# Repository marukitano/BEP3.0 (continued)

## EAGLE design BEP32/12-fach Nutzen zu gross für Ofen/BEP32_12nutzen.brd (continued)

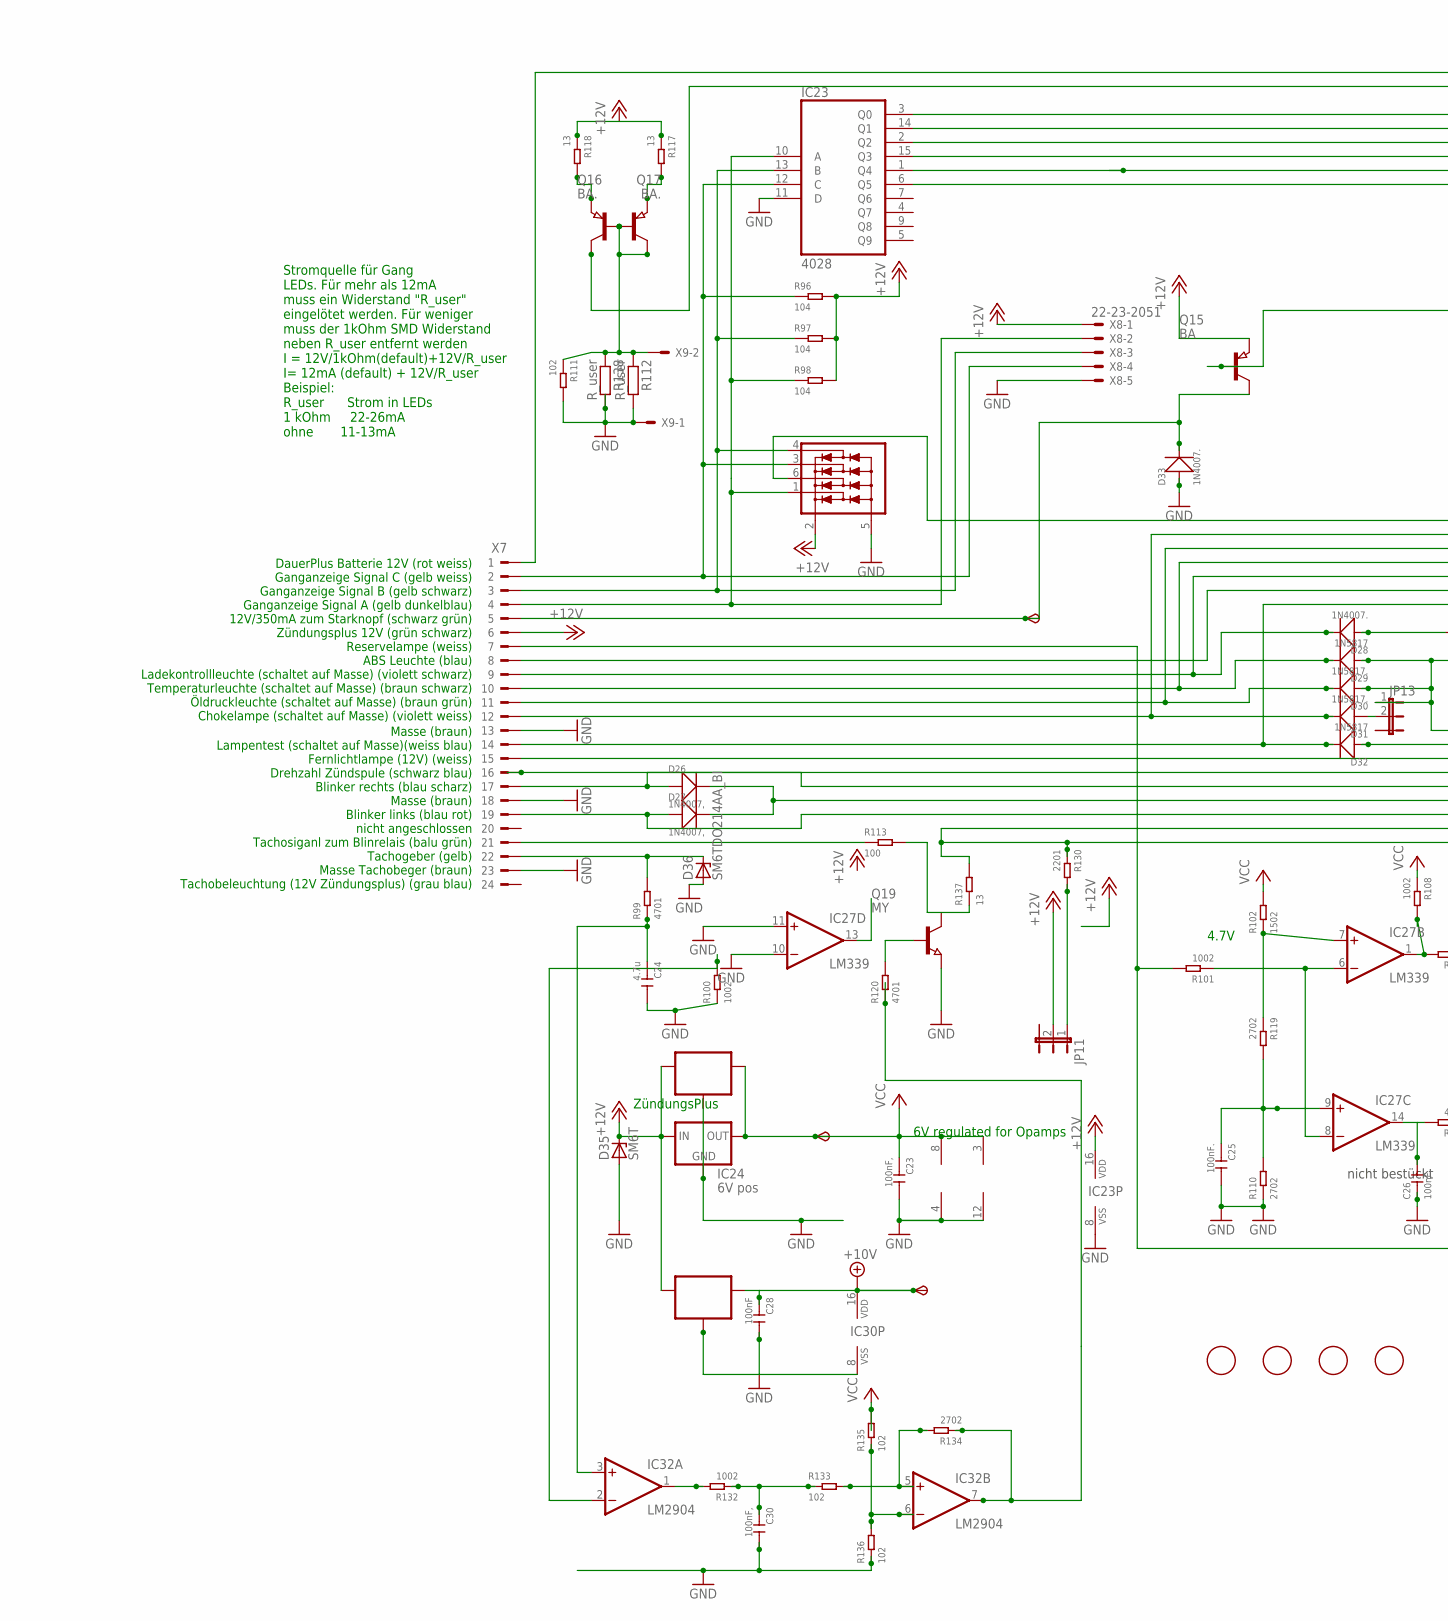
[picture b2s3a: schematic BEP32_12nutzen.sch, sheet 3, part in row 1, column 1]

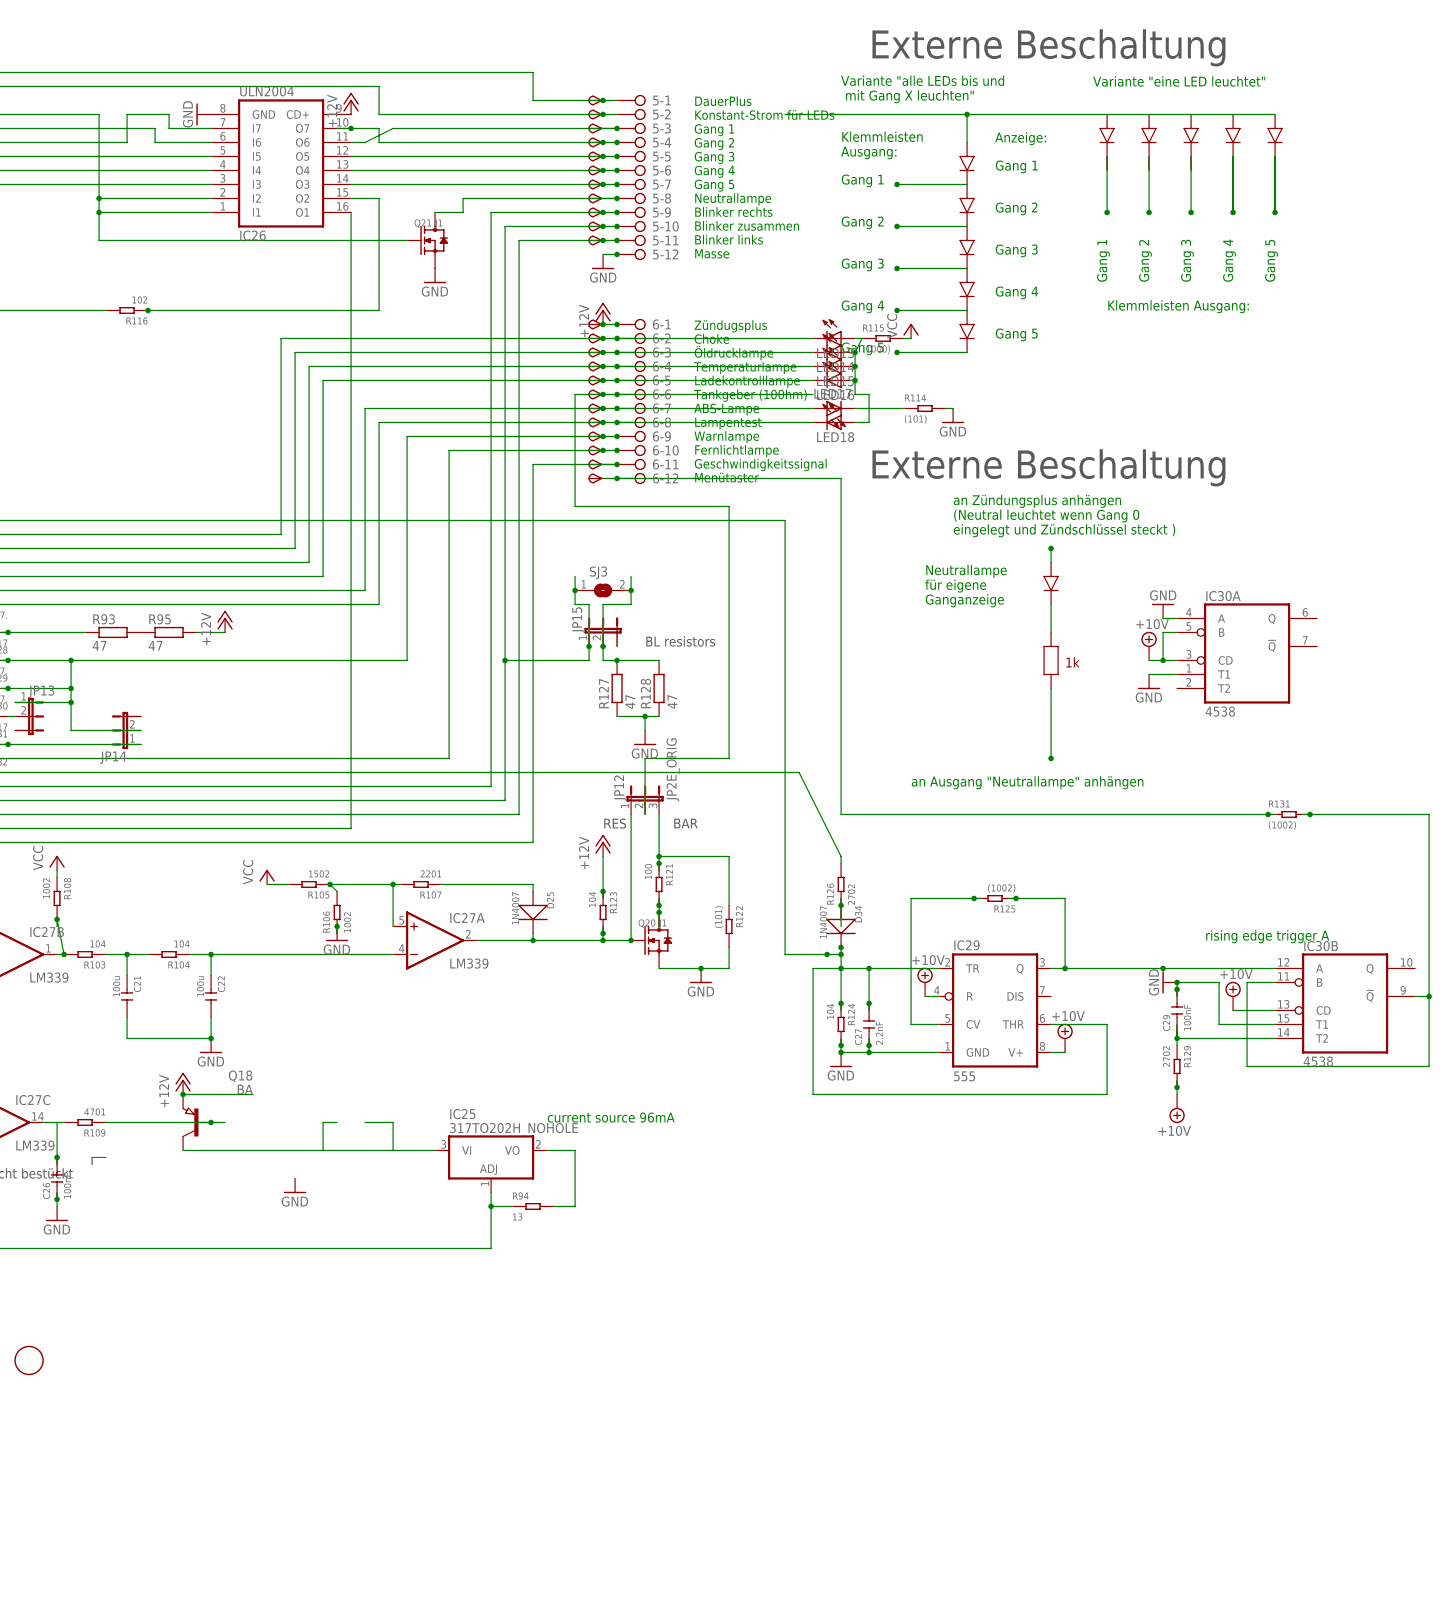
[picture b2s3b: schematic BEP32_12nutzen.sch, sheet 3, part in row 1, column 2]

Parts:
5, 6: 2081-1132; 12-PIN
6V2, 10V2: TPSB2.0; B2.0
C21, C22: 100u; C1206
C23, C30: 100nF,; C0805
C24: 4.7u; C0805
C25, C26: 100nF.; C0805
C27: 2.2nF; C0805
C28, C29: 100nF; C0805
D25, D34: 1N4007; DO-214AC
D26, D27: 1N4007,; DO-214AC
D28, D33: 1N4007.; DO-214AC
D29, D32: 1N5817; DO-214AC_SLIM
D30, D31: 1N5817.; DO-214AC_SLIM
D35: SM6T; DO214AA
D36: SM6TDO214AA_BI; DO214AA_BI
FID9, FID10, FID11, FID12: FIDUCIAL; FIDUCIAL_1MM
IC23: 4028; SO16
IC24: 6V pos; 78LXX
IC25: 317TO202H_NOHOLE; TO220H_NOHOLE
IC26: ULN2004; SO16
IC27: LM339; SO14
IC28: 78L06; SOT89_ROUND
IC29: 555; SO08
IC30: 4538; SO16
IC31: 78L10; SOT89_ROUND
IC32: LM2904; SO08
IC33: NUP4304SOT457_R; SOT457R_PHILIPS
JP11, JP13, JP14, JP15: JP2EJP2_SMALLPADS; JP2_SMALLPADS
JP12: JP2E_ORIG; JP2_ORIG_SMALLPADS
LED13, LED14, LED15, LED16, LED17, LED18: LEDLD260; LD260
Q15, Q18: BA; SOT89
Q16, Q17: BA.; SOT89
Q19: MY; SOT89
Q20, Q21: J1; SOT-23
R93, R95, R127, R128: 47; V235/17_1MM
R94, R117, R118, R137: 13; R1206
R96, R97, R98, R103, R104, R123, R124: 104; R0805
R99, R109, R120: 4701; R0805
R100, R101, R106, R108, R132: 1002; R0805
R102, R105: 1502; R0805
R107, R130: 2201; R0805
R110, R119, R126, R129, R134: 2702; R0805
R111, R116, R133, R135, R136: 102; R0805
R112, R138: R_user; R0805
R113, R121: 100; R0805
R114, R122: (101); R0805
R115: (1000); R0805
R125, R131: (1002); R0805
SJ3: SJ
START2: TPSB2.0; B2.0
TP47, TP48, TP49, TP50, TP51, TP52, TP53, TP54, TP55, TP56, TP57, TP58, TP59, TP60, TP61, TP62, TP63, TP64, TP66, TP67, TP68, TP69: TPSB2.0; B2.0
TP65: TPSB1,27; B1,27
X7: CON_BMWV2; 24-PIN_V2
X8: 22-23-2051
X9: 22-23-2021

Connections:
+10V: 10V2.TP, C28.1, IC29.4 (R), IC29.8 (V+), IC30.3 (CD), IC30.5 (B), IC30.13 (CD), IC30.16 (VDD), IC31.1 (OUT), R129.2; also elsewhere on the board
+12V: 6.1, D35.C, IC23.16 (VDD), IC24.IN, IC26.9 (CD+), IC28.3 (IN), IC31.3 (IN), IC33.2 (V+), JP11.2, Q15.3 (E), Q18.3 (E), R95.2, R96.2, R97.2, R98.2, R117.1, R118.1, R123.1, TP68.TP, X7.6, X8.1; also elsewhere on the board
+12V3: IC32.7 (OUT), R120.1, R134.1
GND: 5.12, C21.2, C22.2, C23.2, C24.2, C25.2, C26.1, C27.1, C28.2, C29.2, C30.2, D33.1 (+), D35.A, D36.A, IC23.8 (VSS), IC23.11 (D), IC24.GND, IC26.8 (GND), IC27.10 (-IN), IC27.11 (+IN), IC27.12 (GND), IC28.2 (GND), IC28.2@1 (GND), IC29.1 (GND), IC30.1 (T1), IC30.4 (A), IC30.8 (VSS), IC30.15 (T1), IC31.2 (GND), IC31.2@1 (GND), IC32.4 (V-), IC33.5 (V-), Q19.3 (E), Q20.2 (S), Q21.2 (S), R100.1, R106.1, R110.1, R111.2, R112.2, R114.2, R122.2, R124.2, R127.1, R128.1, R136.1, R138.2, X7.13, X7.18, X7.23, X8.5, X9.1; also elsewhere on the board
unnamed: R93.2, R95.1
unnamed: 6.9, D29.1 (+), D30.1 (+), JP13.1, JP14.2, TP65.TP
unnamed: IC23.10 (A), IC33.1 (D1), R98.1, X7.4, X8.2
unnamed: IC23.13 (B), IC33.4 (D4), R97.1, X7.3, X8.3
unnamed: D33.2 (-), Q15.2 (C), START2.TP, X7.5
unnamed: IC23.12 (C), IC33.3 (D3), R96.1, X7.2, X8.4
unnamed: 6.7, LED17.A, TP63.TP, X7.8
unnamed: 6.2, D31.2 (-), LED13.K (C), TP58.TP, X7.12
unnamed: 6.3, D30.2 (-), LED14.K (C), TP59.TP, X7.11
unnamed: 6.4, D29.2 (-), LED15.K (C), TP60.TP, X7.10
unnamed: 6.8, D32.2 (-), LED18.K (C), TP64.TP, X7.14
unnamed: 5.9, D26.1 (+), TP55.TP, X7.17
unnamed: 5.11, D27.1 (+), TP57.TP, X7.19
unnamed: D36.C, R99.2, X7.22
unnamed: C24.1, IC32.3 (+IN), R99.1
unnamed: 6.11, IC26.16 (O1), R130.1, R137.2, TP67.TP
unnamed: IC27.1 (OUT), R103.2, R108.2
unnamed: C21.1, R103.1, R104.2
unnamed: C22.1, IC27.4 (-IN), R104.1
unnamed: IC27.5 (+IN), R105.1, R106.2, R107.2
unnamed: D25.1 (+), R107.1
unnamed: C25.1, IC27.9 (+IN), R110.2, R119.2
unnamed: C26.2, IC27.14 (OUT), R109.2
unnamed: Q18.1 (B), R109.1
unnamed: IC23.2 (Q2), IC26.7 (I7)
unnamed: 5.5, IC26.12 (O5), TP51.TP
unnamed: IC23.1 (Q4), IC26.4 (I4)
unnamed: 5.8, Q21.3 (D), TP54.TP
unnamed: 6.10, TP66.TP, X7.15
unnamed: 6.5, D28.2 (-), LED16.K (C), TP61.TP, X7.9
unnamed: D28.1 (+), R93.1
unnamed: IC23.6 (Q5), IC26.3 (I3)
unnamed: 5.4, IC26.10 (O7), TP50.TP
unnamed: IC25.1 (ADJ), R94.1, R101.2, X7.7
unnamed: IC27.6 (-IN), IC27.8 (-IN), R101.1
unnamed: 5.2, Q17.2 (C), TP48.TP
unnamed: 5.1, TP47.TP, X7.1
unnamed: R126.2, X7.16
unnamed: IC23.15 (Q3), IC26.5 (I5)
unnamed: 5.6, IC26.13 (O4), TP52.TP
unnamed: 5.7, IC26.14 (O3), TP53.TP
unnamed: 6.6, JP12.2, TP62.TP
unnamed: LED17.K (C), R114.1
unnamed: LED13.A, LED14.A, LED15.A, LED16.A, LED18.A, R115.1
unnamed: Q15.1 (B), R116.2
unnamed: IC23.3 (Q0), IC26.1 (I1), IC26.2 (I2), Q21.1 (G)
unnamed: IC23.14 (Q1), IC26.6 (I6)
unnamed: 5.3, IC26.11 (O6), TP49.TP
unnamed: Q16.1 (B), Q16.2 (C), Q17.1 (B), R111.1, R112.1, R138.1, X9.2
unnamed: Q17.3 (E), R118.2
unnamed: Q16.3 (E), R117.2
unnamed: IC27.7 (+IN), R102.1, R119.1
unnamed: IC32.2 (-IN), R100.2
unnamed: Q19.1 (B), R120.2
unnamed: Q20.3 (D), R121.2
unnamed: IC25.2 (VO), R94.2
unnamed: IC25.3 (VI), Q18.2 (C)
unnamed: C27.2, D34.2 (-), IC29.2 (TR), IC29.6 (THR), IC33.6 (D2), R124.1
unnamed: IC29.5 (CV), R125.2
unnamed: IC29.3 (Q), IC30.12 (A), R125.1
unnamed: D34.1 (+), R126.1
unnamed: 5.10, D26.2 (-), D27.2 (-), JP15.1, SJ3.1, TP56.TP
unnamed: JP15.2, R127.2, R128.2, SJ3.2
unnamed: IC30.9 (!Q), IC30.11 (B), R131.2
unnamed: C29.1, IC30.14 (T2), R129.1
unnamed: JP11.1, R130.2
unnamed: IC26.15 (O2), R116.1
unnamed: 6.12, R131.1, TP69.TP
unnamed: D31.1 (+), JP13.2
unnamed: D25.2 (-), IC27.2 (OUT), JP12.1, Q20.1 (G), R123.2
unnamed: IC32.1 (OUT), R132.2
unnamed: C30.1, R132.1, R133.1
unnamed: IC32.5 (+IN), R133.2, R134.2
unnamed: IC32.6 (-IN), R135.1, R136.2
unnamed: D32.1 (+), JP14.1
unnamed: JP12.3, R121.1, R122.1
unnamed: R113.1, X7.21
unnamed: Q19.2 (C), R113.2, R137.1
VCC: 6V2.TP, C23.1, IC24.OUT, IC27.3 (V+), IC28.1 (OUT), IC32.8 (V+), R102.2, R105.2, R108.1, R115.2, R135.2; also elsewhere on the board

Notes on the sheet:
6V regulated for Opamps
current source 96mA
ZündungsPlus
Zündugsplus Choke Öldrucklampe Temperaturlampe Ladekontrolllampe Tankgeber (100hm) ABS-Lampe Lampentest Warnlampe Fernlichtlampe Geschwindigkeitssignal Menütaster
DauerPlus Konstant-Strom für LEDs Gang 1 Gang 2 Gang 3 Gang 4 Gang 5 Neutrallampe Blinker rechts Blinker zusammen Blinker links Masse
DauerPlus Batterie 12V (rot weiss) Ganganzeige Signal C (gelb weiss) Ganganzeige Signal B (gelb schwarz) Ganganzeige Signal A (gelb dunkelblau) 12V/350mA zum Starknopf (schwarz grün) Zündungsplus 12V (grün schwarz) Reservelampe (weiss) ABS Leuchte (blau) Ladekontrollleuchte (schaltet auf Masse) (vi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
Masse (braun) Lampentest (schaltet auf Masse)(weiss blau) Fernlichtlampe (12V) (weiss) Drehzahl Zündspule (schwarz blau) Blinker rechts (blau scharz) Masse (braun) Blinker links (blau rot) nicht angeschlossen Tachosiganl zum Blinrelais (balu grün) Tachogeber (gelb) Masse Tachobeger (braun) Tachobel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
4.7V
Stromquelle für Gang LEDs. Für mehr als 12mA muss ein Widerstand "R_user" eingelötet werden. Für weniger muss der 1kOhm SMD Widerstand neben R_user entfernt werden I = 12V/1kOhm(default)+12V/R_user I= 12mA (default) + 12V/R_user Beispiel: R_user Strom in LEDs 1 kOhm 22-26mA ohne 11-13mA
Gang 1
Gang 2
Gang 3
Gang 4
Gang 5
Variante "eine LED leuchtet"
Variante "alle LEDs bis und mit Gang X leuchten"
Klemmleisten Ausgang:
Klemmleisten Ausgang:
an Zündungsplus anhängen (Neutral leuchtet wenn Gang 0 eingelegt und Zündschlüssel steckt )
an Ausgang "Neutrallampe" anhängen
Neutrallampe für eigene Ganganzeige
Externe Beschaltung
Anzeige:
nicht bestückt
rising edge trigger A
BAR
RES
BL resistors

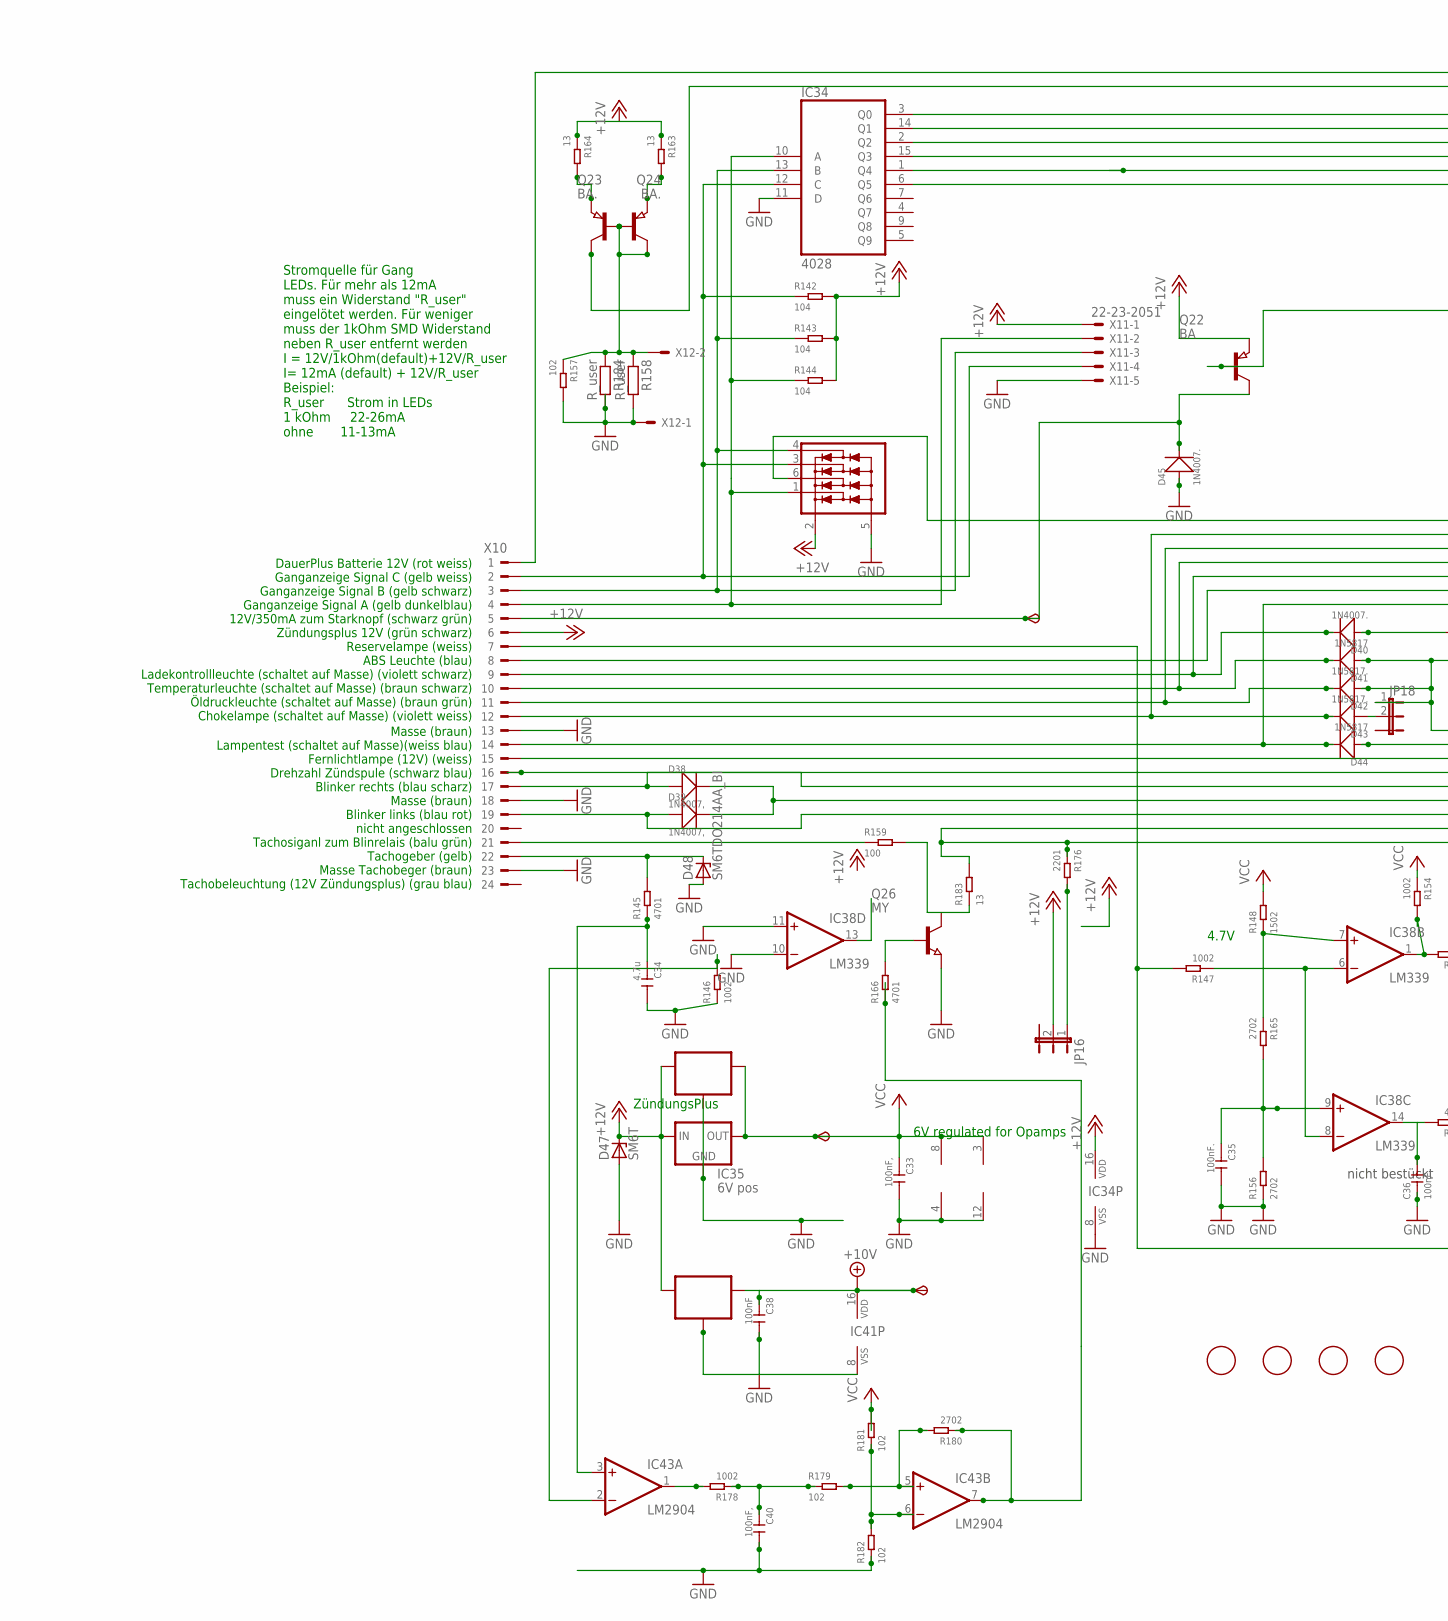
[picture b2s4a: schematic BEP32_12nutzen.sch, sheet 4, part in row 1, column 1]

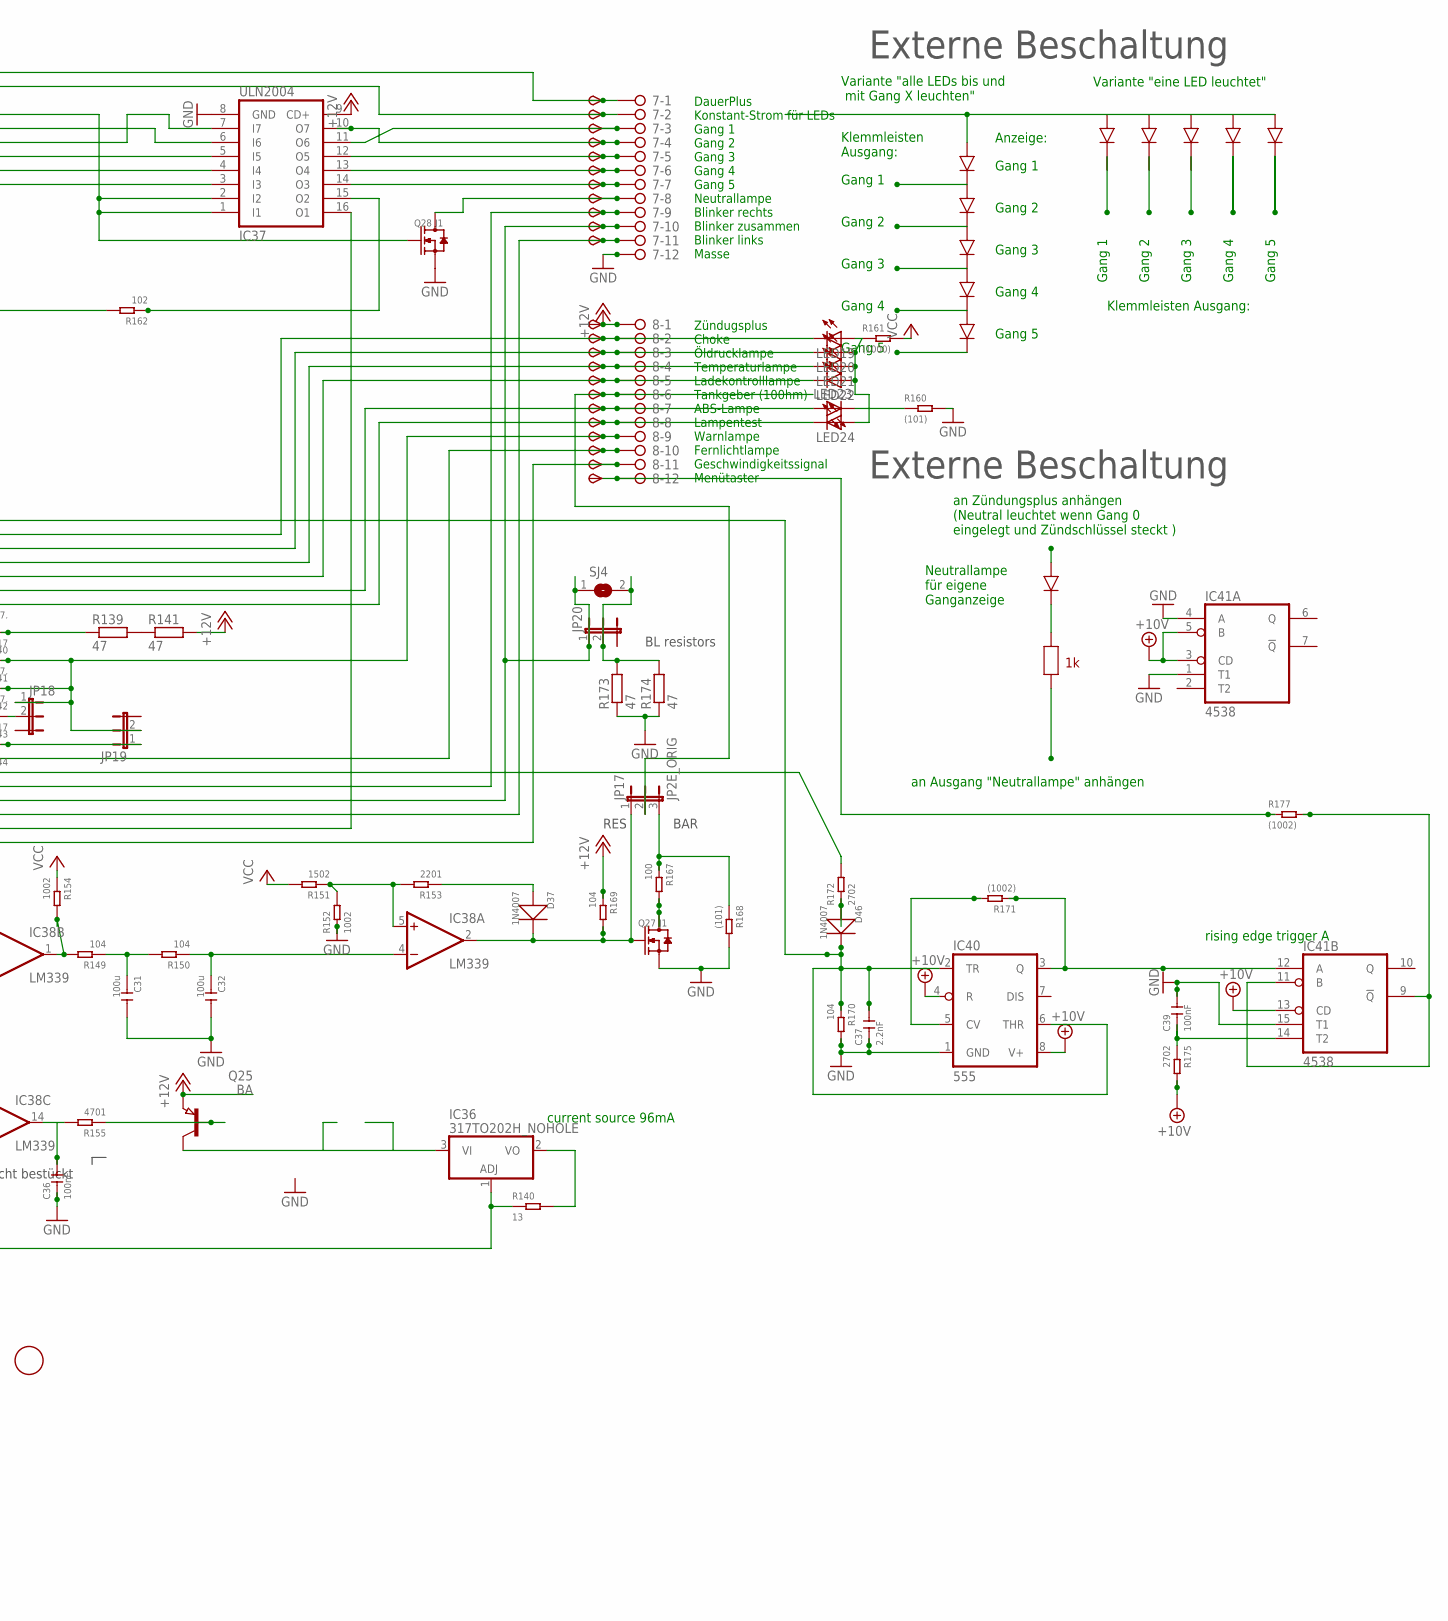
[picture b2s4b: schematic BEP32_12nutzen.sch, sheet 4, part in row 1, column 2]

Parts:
6V3, 10V3: TPSB2.0; B2.0
7, 8: 2081-1132; 12-PIN
C31, C32: 100u; C1206
C33, C40: 100nF,; C0805
C34: 4.7u; C0805
C35, C36: 100nF.; C0805
C37: 2.2nF; C0805
C38, C39: 100nF; C0805
D37, D46: 1N4007; DO-214AC
D38, D39: 1N4007,; DO-214AC
D40, D45: 1N4007.; DO-214AC
D41, D44: 1N5817; DO-214AC_SLIM
D42, D43: 1N5817.; DO-214AC_SLIM
D47: SM6T; DO214AA
D48: SM6TDO214AA_BI; DO214AA_BI
FID13, FID14, FID15, FID16: FIDUCIAL; FIDUCIAL_1MM
IC34: 4028; SO16
IC35: 6V pos; 78LXX
IC36: 317TO202H_NOHOLE; TO220H_NOHOLE
IC37: ULN2004; SO16
IC38: LM339; SO14
IC39: 78L06; SOT89_ROUND
IC40: 555; SO08
IC41: 4538; SO16
IC42: 78L10; SOT89_ROUND
IC43: LM2904; SO08
IC44: NUP4304SOT457_R; SOT457R_PHILIPS
JP16, JP18, JP19, JP20: JP2EJP2_SMALLPADS; JP2_SMALLPADS
JP17: JP2E_ORIG; JP2_ORIG_SMALLPADS
LED19, LED20, LED21, LED22, LED23, LED24: LEDLD260; LD260
Q22, Q25: BA; SOT89
Q23, Q24: BA.; SOT89
Q26: MY; SOT89
Q27, Q28: J1; SOT-23
R139, R141, R173, R174: 47; V235/17_1MM
R140, R163, R164, R183: 13; R1206
R142, R143, R144, R149, R150, R169, R170: 104; R0805
R145, R155, R166: 4701; R0805
R146, R147, R152, R154, R178: 1002; R0805
R148, R151: 1502; R0805
R153, R176: 2201; R0805
R156, R165, R172, R175, R180: 2702; R0805
R157, R162, R179, R181, R182: 102; R0805
R158, R184: R_user; R0805
R159, R167: 100; R0805
R160, R168: (101); R0805
R161: (1000); R0805
R171, R177: (1002); R0805
SJ4: SJ
START3: TPSB2.0; B2.0
TP70, TP71, TP72, TP73, TP74, TP75, TP76, TP77, TP78, TP79, TP80, TP81, TP82, TP83, TP84, TP85, TP86, TP87, TP89, TP90, TP91, TP92: TPSB2.0; B2.0
TP88: TPSB1,27; B1,27
X10: CON_BMWV2; 24-PIN_V2
X11: 22-23-2051
X12: 22-23-2021

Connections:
+10V: 10V3.TP, C38.1, IC40.4 (R), IC40.8 (V+), IC41.3 (CD), IC41.5 (B), IC41.13 (CD), IC41.16 (VDD), IC42.1 (OUT), R175.2; also elsewhere on the board
+12V: 8.1, D47.C, IC34.16 (VDD), IC35.IN, IC37.9 (CD+), IC39.3 (IN), IC42.3 (IN), IC44.2 (V+), JP16.2, Q22.3 (E), Q25.3 (E), R141.2, R142.2, R143.2, R144.2, R163.1, R164.1, R169.1, TP91.TP, X10.6, X11.1; also elsewhere on the board
+12V4: IC43.7 (OUT), R166.1, R180.1
GND: 7.12, C31.2, C32.2, C33.2, C34.2, C35.2, C36.1, C37.1, C38.2, C39.2, C40.2, D45.1 (+), D47.A, D48.A, IC34.8 (VSS), IC34.11 (D), IC35.GND, IC37.8 (GND), IC38.10 (-IN), IC38.11 (+IN), IC38.12 (GND), IC39.2 (GND), IC39.2@1 (GND), IC40.1 (GND), IC41.1 (T1), IC41.4 (A), IC41.8 (VSS), IC41.15 (T1), IC42.2 (GND), IC42.2@1 (GND), IC43.4 (V-), IC44.5 (V-), Q26.3 (E), Q27.2 (S), Q28.2 (S), R146.1, R152.1, R156.1, R157.2, R158.2, R160.2, R168.2, R170.2, R173.1, R174.1, R182.1, R184.2, X10.13, X10.18, X10.23, X11.5, X12.1; also elsewhere on the board
unnamed: R139.2, R141.1
unnamed: 8.9, D41.1 (+), D42.1 (+), JP18.1, JP19.2, TP88.TP
unnamed: IC34.10 (A), IC44.1 (D1), R144.1, X10.4, X11.2
unnamed: IC34.13 (B), IC44.4 (D4), R143.1, X10.3, X11.3
unnamed: D45.2 (-), Q22.2 (C), START3.TP, X10.5
unnamed: IC34.12 (C), IC44.3 (D3), R142.1, X10.2, X11.4
unnamed: 8.7, LED23.A, TP86.TP, X10.8
unnamed: 8.2, D43.2 (-), LED19.K (C), TP81.TP, X10.12
unnamed: 8.3, D42.2 (-), LED20.K (C), TP82.TP, X10.11
unnamed: 8.4, D41.2 (-), LED21.K (C), TP83.TP, X10.10
unnamed: 8.8, D44.2 (-), LED24.K (C), TP87.TP, X10.14
unnamed: 7.9, D38.1 (+), TP78.TP, X10.17
unnamed: 7.11, D39.1 (+), TP80.TP, X10.19
unnamed: D48.C, R145.2, X10.22
unnamed: C34.1, IC43.3 (+IN), R145.1
unnamed: 8.11, IC37.16 (O1), R176.1, R183.2, TP90.TP
unnamed: IC38.1 (OUT), R149.2, R154.2
unnamed: C31.1, R149.1, R150.2
unnamed: C32.1, IC38.4 (-IN), R150.1
unnamed: IC38.5 (+IN), R151.1, R152.2, R153.2
unnamed: D37.1 (+), R153.1
unnamed: C35.1, IC38.9 (+IN), R156.2, R165.2
unnamed: C36.2, IC38.14 (OUT), R155.2
unnamed: Q25.1 (B), R155.1
unnamed: IC34.2 (Q2), IC37.7 (I7)
unnamed: 7.5, IC37.12 (O5), TP74.TP
unnamed: IC34.1 (Q4), IC37.4 (I4)
unnamed: 7.8, Q28.3 (D), TP77.TP
unnamed: 8.10, TP89.TP, X10.15
unnamed: 8.5, D40.2 (-), LED22.K (C), TP84.TP, X10.9
unnamed: D40.1 (+), R139.1
unnamed: IC34.6 (Q5), IC37.3 (I3)
unnamed: 7.4, IC37.10 (O7), TP73.TP
unnamed: IC36.1 (ADJ), R140.1, R147.2, X10.7
unnamed: IC38.6 (-IN), IC38.8 (-IN), R147.1
unnamed: 7.2, Q24.2 (C), TP71.TP
unnamed: 7.1, TP70.TP, X10.1
unnamed: R172.2, X10.16
unnamed: IC34.15 (Q3), IC37.5 (I5)
unnamed: 7.6, IC37.13 (O4), TP75.TP
unnamed: 7.7, IC37.14 (O3), TP76.TP
unnamed: 8.6, JP17.2, TP85.TP
unnamed: LED23.K (C), R160.1
unnamed: LED19.A, LED20.A, LED21.A, LED22.A, LED24.A, R161.1
unnamed: Q22.1 (B), R162.2
unnamed: IC34.3 (Q0), IC37.1 (I1), IC37.2 (I2), Q28.1 (G)
unnamed: IC34.14 (Q1), IC37.6 (I6)
unnamed: 7.3, IC37.11 (O6), TP72.TP
unnamed: Q23.1 (B), Q23.2 (C), Q24.1 (B), R157.1, R158.1, R184.1, X12.2
unnamed: Q24.3 (E), R164.2
unnamed: Q23.3 (E), R163.2
unnamed: IC38.7 (+IN), R148.1, R165.1
unnamed: IC43.2 (-IN), R146.2
unnamed: Q26.1 (B), R166.2
unnamed: Q27.3 (D), R167.2
unnamed: IC36.2 (VO), R140.2
unnamed: IC36.3 (VI), Q25.2 (C)
unnamed: C37.2, D46.2 (-), IC40.2 (TR), IC40.6 (THR), IC44.6 (D2), R170.1
unnamed: IC40.5 (CV), R171.2
unnamed: IC40.3 (Q), IC41.12 (A), R171.1
unnamed: D46.1 (+), R172.1
unnamed: 7.10, D38.2 (-), D39.2 (-), JP20.1, SJ4.1, TP79.TP
unnamed: JP20.2, R173.2, R174.2, SJ4.2
unnamed: IC41.9 (!Q), IC41.11 (B), R177.2
unnamed: C39.1, IC41.14 (T2), R175.1
unnamed: JP16.1, R176.2
unnamed: IC37.15 (O2), R162.1
unnamed: 8.12, R177.1, TP92.TP
unnamed: D43.1 (+), JP18.2
unnamed: D37.2 (-), IC38.2 (OUT), JP17.1, Q27.1 (G), R169.2
unnamed: IC43.1 (OUT), R178.2
unnamed: C40.1, R178.1, R179.1
unnamed: IC43.5 (+IN), R179.2, R180.2
unnamed: IC43.6 (-IN), R181.1, R182.2
unnamed: D44.1 (+), JP19.1
unnamed: JP17.3, R167.1, R168.1
unnamed: R159.1, X10.21
unnamed: Q26.2 (C), R159.2, R183.1
VCC: 6V3.TP, C33.1, IC35.OUT, IC38.3 (V+), IC39.1 (OUT), IC43.8 (V+), R148.2, R151.2, R154.1, R161.2, R181.2; also elsewhere on the board

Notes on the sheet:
6V regulated for Opamps
current source 96mA
ZündungsPlus
Zündugsplus Choke Öldrucklampe Temperaturlampe Ladekontrolllampe Tankgeber (100hm) ABS-Lampe Lampentest Warnlampe Fernlichtlampe Geschwindigkeitssignal Menütaster
DauerPlus Konstant-Strom für LEDs Gang 1 Gang 2 Gang 3 Gang 4 Gang 5 Neutrallampe Blinker rechts Blinker zusammen Blinker links Masse
DauerPlus Batterie 12V (rot weiss) Ganganzeige Signal C (gelb weiss) Ganganzeige Signal B (gelb schwarz) Ganganzeige Signal A (gelb dunkelblau) 12V/350mA zum Starknopf (schwarz grün) Zündungsplus 12V (grün schwarz) Reservelampe (weiss) ABS Leuchte (blau) Ladekontrollleuchte (schaltet auf Masse) (vi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
Masse (braun) Lampentest (schaltet auf Masse)(weiss blau) Fernlichtlampe (12V) (weiss) Drehzahl Zündspule (schwarz blau) Blinker rechts (blau scharz) Masse (braun) Blinker links (blau rot) nicht angeschlossen Tachosiganl zum Blinrelais (balu grün) Tachogeber (gelb) Masse Tachobeger (braun) Tachobel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
4.7V
Stromquelle für Gang LEDs. Für mehr als 12mA muss ein Widerstand "R_user" eingelötet werden. Für weniger muss der 1kOhm SMD Widerstand neben R_user entfernt werden I = 12V/1kOhm(default)+12V/R_user I= 12mA (default) + 12V/R_user Beispiel: R_user Strom in LEDs 1 kOhm 22-26mA ohne 11-13mA
Gang 1
Gang 2
Gang 3
Gang 4
Gang 5
Variante "eine LED leuchtet"
Variante "alle LEDs bis und mit Gang X leuchten"
Klemmleisten Ausgang:
Klemmleisten Ausgang:
an Zündungsplus anhängen (Neutral leuchtet wenn Gang 0 eingelegt und Zündschlüssel steckt )
an Ausgang "Neutrallampe" anhängen
Neutrallampe für eigene Ganganzeige
Externe Beschaltung
Anzeige:
nicht bestückt
rising edge trigger A
BAR
RES
BL resistors
